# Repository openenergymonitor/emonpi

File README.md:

# emonPi

Raspberry Pi based energy Monitoring Unit

## Documentation

- [Install Guide](https://docs.openenergymonitor.org/emonpi/install.html)
- [Connect](https://docs.openenergymonitor.org/emonpi/connect.html)
- [Pulse counting](https://docs.openenergymonitor.org/emonpi/pulse_counting.html)
- [Temperature sensing](https://docs.openenergymonitor.org/emonpi/temperature_sensing.html)
- [Firmware](https://docs.openenergymonitor.org/emonpi/firmware.html)
- [Configuration](https://docs.openenergymonitor.org/emonpi/configuration.html)
- [Use in North America](https://docs.openenergymonitor.org/emonpi/north-america.html)
- [Modification](https://docs.openenergymonitor.org/emonpi/modification.html)
- [Technical](https://docs.openenergymonitor.org/emonpi/technical.html)

Or view directly on github [here](docs).

## [emonSD image download](https://docs.openenergymonitor.org/emonsd/download.html)

[Software Stack Build & Documentation](https://github.com/openenergymonitor/emonscripts)

## Open-Hardware:

- [Schematic & Board CAD Design Files](https://github.com/openenergymonitor/emonpi/tree/master/hardware)

## Community & Support

- [OpenEnergyMonitor Forums](https://community.openenergymonitor.org)
- OpenEnergyMonitor Shop Support: support@openenergymonitor.zendesk.com

## License

- The hardware designs (schematics and CAD files) are licensed under a Creative Commons Attribution-ShareAlike 3.0 Unported License.
- The firmware is released under the GNU GPL V3 license The documentation is subject to GNU Free Documentation License
- The hardware designs follow the terms of the OSHW (Open-source hardware) Statement of Principles 1.0.

## Disclaimer

```
OUR PRODUCTS AND ASSEMBLY KITS MAY BE USED BY EXPERIENCED, SKILLED USERS, AT THEIR OWN RISK. TO THE FULLEST EXTENT PERMISSIBLE BY THE APPLICABLE LAW, WE HEREBY DISCLAIM ANY AND ALL RESPONSIBILITY, RISK, LIABILITY AND DAMAGES ARISING OUT OF DEATH OR PERSONAL INJURY RESULTING FROM ASSEMBLY OR OPERATION OF OUR PRODUCTS.

Your safety is your own responsibility, including proper use of equipment and safety gear, and determining whether you have adequate skill and experience. OpenEnergyMonitor and Megni registered partnership disclaims all responsibility for any resulting damage, injury, or expense. It is your responsibility to make sure that your activities comply with applicable laws, including copyright. Always check the webpage associated with each unit before you get started. There may be important updates or corrections. All use of the instructions, kits, projects and suggestions given both by megni.co.uk, openenergymonitor.org and shop.openenergymonitor.org are to be used at your own risk. The technology (hardware , firmware and software) are constantly changing, documentation (including build guide and instructions) may not be complete or correct.

If you feel uncomfortable with assembling or using any part of the system, return it to us for a full refund.
```

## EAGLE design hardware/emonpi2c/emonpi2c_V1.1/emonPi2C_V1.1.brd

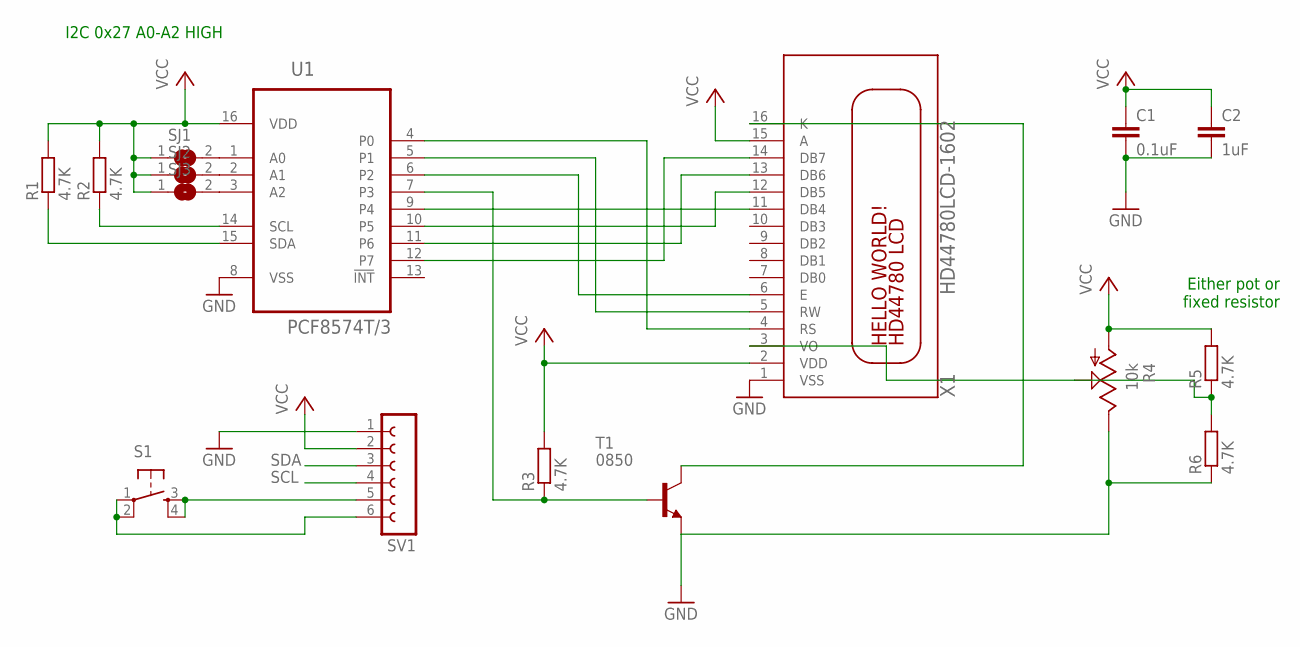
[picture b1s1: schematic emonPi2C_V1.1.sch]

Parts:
C1: 0.1uF; C0603
C2: 1uF; C0603
R1, R2, R3, R5, R6: 4.7K; R0603
R4: 10k; B25P
S1: TAC_SWITCHPTH; TACTILE-PTH
SJ1, SJ2, SJ3: SJ
SV1: FE06-1; FE06
T1: 0850; SOT23
U1: PCF8574T/3; SOIC127P1032X265-16N
X1: HD44780LCD-1602; LCD1602

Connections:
5V: C1.1, C2.1, R1.2, R2.2, R3.2, R4.A, R5.2, SJ1.1, SJ2.1, SJ3.1, SV1.2, U1.16 (VDD), X1.2 (VDD), X1.15 (A)
CS: U1.6 (P2), X1.6 (E)
DB4: U1.9 (P4), X1.11 (DB4)
DB5: U1.10 (P5), X1.12 (DB5)
DB6: U1.11 (P6), X1.13 (DB6)
DB7: U1.12 (P7), X1.14 (DB7)
GND: C1.2, C2.2, R4.E, R6.1, SV1.1, T1.2 (E), U1.8 (VSS), X1.1 (VSS)
K: T1.3 (C), X1.16 (K)
unnamed: SJ3.2, U1.3 (A2)
unnamed: SJ2.2, U1.2 (A1)
unnamed: S1.3, S1.4, SV1.5
unnamed: S1.1, S1.2, SV1.6
unnamed: SJ1.2, U1.1 (A0)
unnamed: R4.S, R5.1, R6.2, X1.3 (VO)
P3: R3.1, T1.1 (B), U1.7 (P3)
RS: U1.4 (P0), X1.4 (RS)
RW: U1.5 (P1), X1.5 (RW)
SCL: R2.1, SV1.4, U1.14 (SCL)
SDA: R1.1, SV1.3, U1.15 (SDA)

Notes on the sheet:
Either pot or fixed resistor
I2C 0x27 A0-A2 HIGH

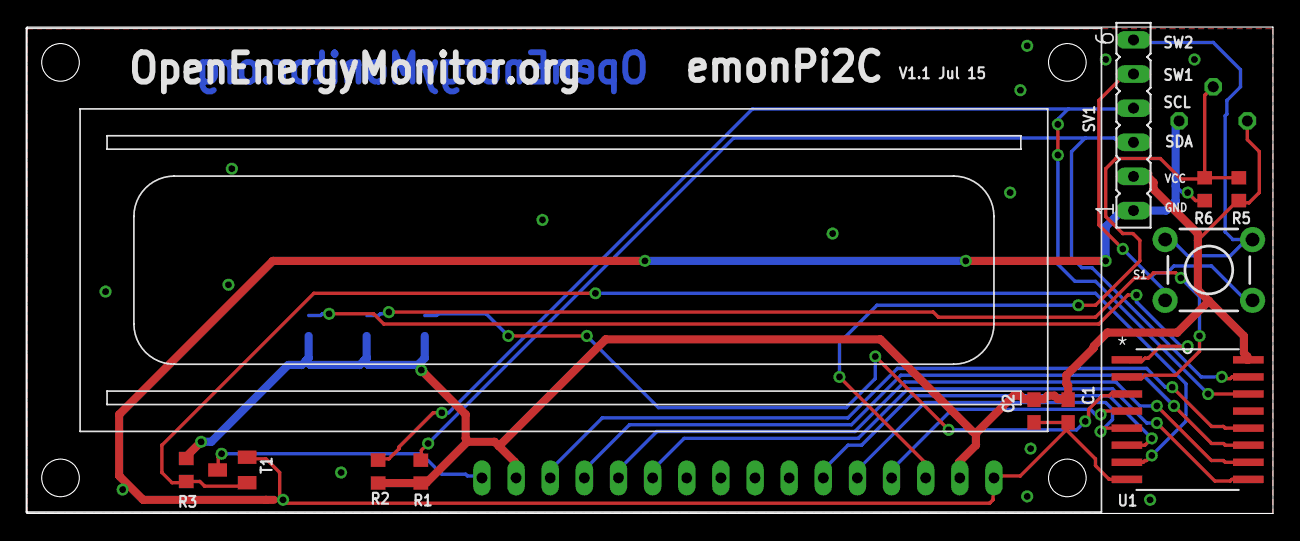
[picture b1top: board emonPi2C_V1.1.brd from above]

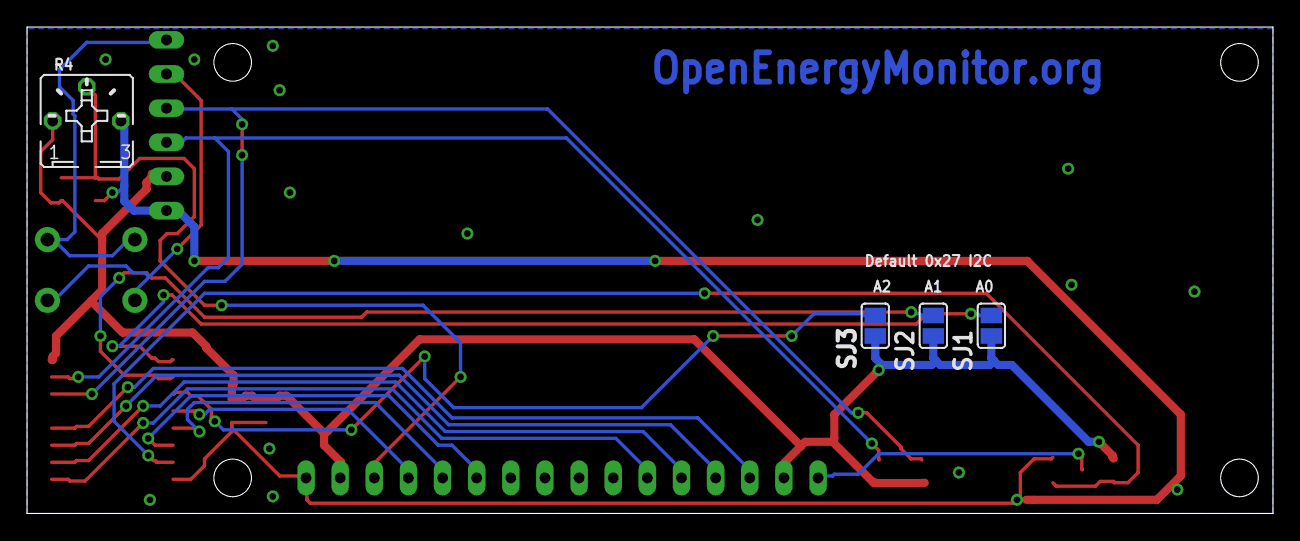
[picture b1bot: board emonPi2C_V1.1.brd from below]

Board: 2 copper layers, 92.7 x 36.2 mm, 16 parts (4 on the bottom side), 19 nets.

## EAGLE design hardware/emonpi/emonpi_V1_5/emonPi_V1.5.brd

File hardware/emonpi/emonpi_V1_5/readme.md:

## emonPi V1.5

**Raspberry Pi Energy Monitoring Shield**

### Schematic

### Board

### Open Hardware

Hardware designs (schematics and CAD) files are licensed under the [Creative Commons Attribution-ShareAlike 3.0 Unported License](http://creativecommons.org/licenses/by-sa/3.0/) and follow the terms of the [OSHW (Open-source hardware) Statement of Principles 1.0.](http://freedomdefined.org/OSHW)

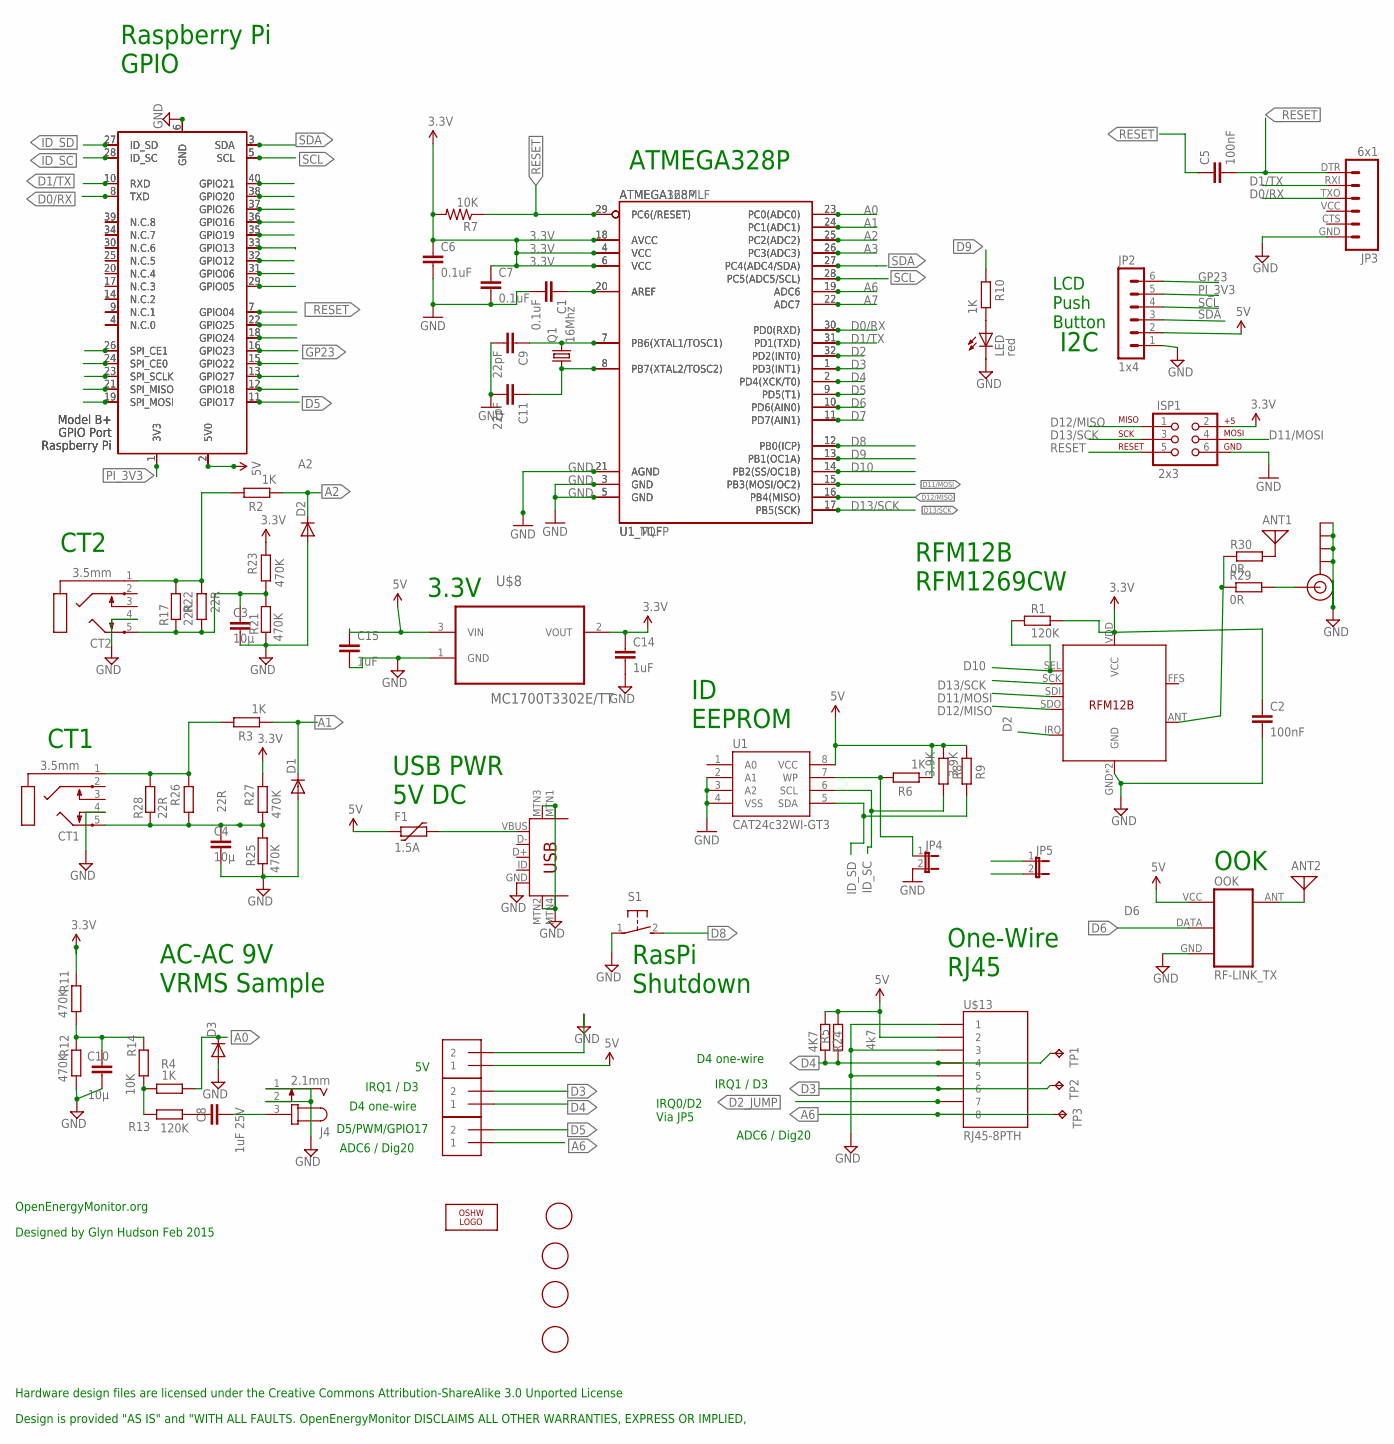
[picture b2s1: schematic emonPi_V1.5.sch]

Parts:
ANT1, ANT2: ANTENNA; PAD-01
C1, C6, C7: 0.1uF; C0603
C2, C5: 100nF; C0603
C3, C4, C10: 10µ; C0603
C8: 1uF 25V; C0603
C9, C11: 22pF; C0603
C14, C15: 1uF; C0603
CT1, CT2: 3.5mm; STX3100
D1, D2, D3: DIODE-SOD523; SOD523
F1: 1.5A; PTC1812L
ISP1: 2x3; 2X3
J1, J2, J3: 1X2-3.5MM
J4: 2.1mm; SPC4077
J$1: SMA_EDGE; SMA-EDGE
JP2: 1x4; MA06-1
JP3: 6x1; FTDI_BASIC
JP4, JP5: JUMPER-2PTH; 1X02
LED: red; CHIPLED_0805
LOGO1: OSHW_LOGO_10MILX0200-NT; OSHW_10X200_NOTEXT
OOK: RF-LINK_TX
Q1: 16Mhz; HC49UP
R1, R13: 120K; R0603
R2, R3, R4, R6, R10: 1K; R0603
R5: 4k7; 0204/7
R7, R14: 10K; R0603
R8, R9: 3.9K; R0603
R11, R12, R21, R23, R25, R27: 470K; R0603
R17, R28: 22R; R1206
R22, R26: 22R; 0204/7
R24: 4K7; R0603
R29, R30: 0R; R0603
S1: 31-XX; B3F-31XX
TP1, TP2, TP3: TPPAD1-13; P1-13
U1: CAT24c32WI-GT3; SO08
U1_MLF: ATMEGA168MLF; MLF32
U1_TQFP: ATMEGA328P; TQFP32-08
U$1, U$3, U$4, U$5: FIDUCIAL; FIDUCIAL_1MM
U$7: USB-MINIB-5PIN; USB-MINIB-CISECO
U$8: MC1700T3302E/TT; SOT95P237X112-3N
U$13: RJ45-8PTH; RJ45-8
U$14: RFM12B
X1: RASPI_GPIO_B+_SMT; RASPI_SMT_GPIO_B+_PIN
X4: RASPI_GPIO_B+_PIN

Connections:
3.3V: C2.1, C6.1, C7.1, C14.1, ISP1.2, R1.2, R7.2, R11.2, R23.2, R27.2, U1_MLF.4 (VCC), U1_MLF.6 (VCC), U1_MLF.18 (AVCC), U1_TQFP.4 (VCC), U1_TQFP.6 (VCC), U1_TQFP.18 (AVCC), U$8.2 (VOUT), U$14.VDD (VCC)
5V: C15.1, F1.1, J1.1, JP2.2, OOK.VCC (+5V), R5.2, R6.1, R8.1, R9.1, R24.1, U1.8 (VCC), U$8.3 (VIN), U$13.2, X1.2 (5V0), X4.2 (5V0)
A0: D3.C, R4.1, U1_MLF.23 (PC0(ADC0)), U1_TQFP.23 (PC0(ADC0))
A1: D1.C, R3.1, U1_MLF.24 (PC1(ADC1)), U1_TQFP.24 (PC1(ADC1))
A2: D2.C, R2.1, U1_MLF.25 (PC2(ADC2)), U1_TQFP.25 (PC2(ADC2))
A3: U1_MLF.26 (PC3(ADC3)), U1_TQFP.26 (PC3(ADC3))
A6: J3.1, TP3.TP, U1_MLF.19 (ADC6), U1_TQFP.19 (ADC6), U$13.8
A7: U1_MLF.22 (ADC7), U1_TQFP.22 (ADC7)
D0/RX: JP3.TXO (3), U1_MLF.30 (PD0(RXD)), U1_TQFP.30 (PD0(RXD)), X1.8 (TXD), X4.8 (TXD)
D1/TX: JP3.RXI (2), U1_MLF.31 (PD1(TXD)), U1_TQFP.31 (PD1(TXD)), X1.10 (RXD), X4.10 (RXD)
D2: JP5.1, U1_MLF.32 (PD2(INT0)), U1_TQFP.32 (PD2(INT0)), U$14.IRQ
D2_JUMP: JP5.2, U$13.7
D3: J2.2, TP2.TP, U1_MLF.1 (PD3(INT1)), U1_TQFP.1 (PD3(INT1)), U$13.6
D4: J2.1, R5.1, R24.2, TP1.TP, U1_MLF.2 (PD4(XCK/T0)), U1_TQFP.2 (PD4(XCK/T0)), U$13.4
D5: J3.2, U1_MLF.9 (PD5(T1)), U1_TQFP.9 (PD5(T1)), X1.11 (GPIO17), X4.11 (GPIO17)
D6: OOK.DATA, U1_MLF.10 (PD6(AIN0)), U1_TQFP.10 (PD6(AIN0))
D7: U1_MLF.11 (PD7(AIN1)), U1_TQFP.11 (PD7(AIN1))
D8: S1.2 (S), U1_MLF.12 (PB0(ICP)), U1_TQFP.12 (PB0(ICP))
D9: R10.2, U1_MLF.13 (PB1(OC1A)), U1_TQFP.13 (PB1(OC1A))
D10: R1.1, U1_MLF.14 (PB2(SS/OC1B)), U1_TQFP.14 (PB2(SS/OC1B)), U$14.SEL
D11/MOSI: ISP1.4, U1_MLF.15 (PB3(MOSI/OC2)), U1_TQFP.15 (PB3(MOSI/OC2)), U$14.SDI
D12/MISO: ISP1.1, U1_MLF.16 (PB4(MISO)), U1_TQFP.16 (PB4(MISO)), U$14.SDO
D13/SCK: ISP1.3, U1_MLF.17 (PB5(SCK)), U1_TQFP.17 (PB5(SCK)), U$14.SCK
DIG6: R29.1, R30.1, U$14.ANT
GND: C1.2, C2.2, C3.2, C4.2, C6.2, C7.2, C9.2, C10.2, C11.2, C14.2, C15.2, CT1.4, CT2.4, D1.A, D2.A, D3.A, ISP1.6, J1.2, J4.1, J4.2, J$1.GND@0 (GND), J$1.GND@1 (GND), J$1.GND@2 (GND), J$1.GND@3 (GND), JP2.1, JP3.GND (6), JP4.2, LED.C, OOK.GND, R12.1, R21.2, R25.2, S1.1, U1.2 (A1), U1.3 (A2), U1.4 (VSS), U1_MLF.3 (GND), U1_MLF.5 (GND), U1_MLF.21 (AGND), U1_TQFP.3 (GND), U1_TQFP.5 (GND), U1_TQFP.21 (AGND), U$7.GND, U$7.MTN1 (MTN2), U$7.MTN2 (MTN3), U$7.MTN3 (MTN1), U$7.MTN4, U$8.1 (GND), U$13.1, U$13.3, U$13.5, U$14.GND, U$14.P$12 (GND), X1.6 (GND), X4.6 (GND)
GP23: JP2.6, X1.16 (GPIO23), X4.16 (GPIO23)
ID_SC: R8.2, U1.6 (SCL), X1.28 (ID_SC), X4.28 (ID_SC)
ID_SD: R9.2, U1.5 (SDA), X1.27 (ID_SD), X4.27 (ID_SD)
unnamed: C9.1, Q1.2, U1_MLF.7 (PB6(XTAL1/TOSC1)), U1_TQFP.7 (PB6(XTAL1/TOSC1))
unnamed: C11.1, Q1.1, U1_MLF.8 (PB7(XTAL2/TOSC2)), U1_TQFP.8 (PB7(XTAL2/TOSC2))
unnamed: C3.1, CT2.5, R17.1, R21.1, R22.1, R23.1
unnamed: C8.1, R13.1
unnamed: R4.2, R13.2, R14.1
unnamed: CT1.1, R3.2, R26.2, R28.2
unnamed: ANT1.1, R30.2
unnamed: ANT2.1, OOK.ANT
unnamed: C4.1, CT1.5, R25.1, R26.1, R27.1, R28.1
unnamed: F1.2, U$7.VBUS
unnamed: CT2.1, R2.2, R17.2, R22.2
unnamed: C8.2, J4.3
unnamed: C1.1, U1_MLF.20 (AREF), U1_TQFP.20 (AREF)
unnamed: J$1.SIG (SIGNAL), R29.2
unnamed: X1.12 (GPIO18), X4.12 (GPIO18)
unnamed: X1.13 (GPIO27), X4.13 (GPIO27)
unnamed: X1.15 (GPIO22), X4.15 (GPIO22)
unnamed: C10.1, R11.1, R12.2, R14.2
unnamed: X1.18 (GPIO24), X4.18 (GPIO24)
unnamed: X1.22 (GPIO25), X4.22 (GPIO25)
unnamed: LED.A, R10.1
unnamed: X1.19 (SPI_MOSI), X4.19 (SPI_MOSI)
unnamed: X1.21 (SPI_MISO), X4.21 (SPI_MISO)
unnamed: X1.23 (SPI_SCLK), X4.23 (SPI_SCLK)
unnamed: X1.24 (SPI_CE0), X4.24 (SPI_CE0)
unnamed: X1.26 (SPI_CE1), X4.26 (SPI_CE1)
unnamed: X1.4 (N.C.0), X4.4 (N.C.0)
unnamed: X1.9 (N.C.1), X4.9 (N.C.1)
unnamed: X1.14 (N.C.2), X4.14 (N.C.2)
unnamed: X1.17 (N.C.3), X4.17 (N.C.3)
unnamed: X1.20 (N.C.4), X4.20 (N.C.4)
unnamed: X1.25 (N.C.5), X4.25 (N.C.5)
unnamed: X1.29 (GPIO05), X4.29 (GPIO05)
unnamed: X1.31 (GPIO06), X4.31 (GPIO06)
unnamed: X1.32 (GPIO12), X4.32 (GPIO12)
unnamed: X1.33 (GPIO13), X4.33 (GPIO13)
unnamed: X1.35 (GPIO19), X4.35 (GPIO19)
unnamed: X1.36 (GPIO16), X4.36 (GPIO16)
unnamed: X1.37 (GPIO26), X4.37 (GPIO26)
unnamed: X1.38 (GPIO20), X4.38 (GPIO20)
unnamed: X1.40 (GPIO21), X4.40 (GPIO21)
unnamed: X1.30 (N.C.6), X4.30 (N.C.6)
unnamed: X1.34 (N.C.7), X4.34 (N.C.7)
unnamed: X1.39 (N.C.8), X4.39 (N.C.8)
unnamed: JP4.1, R6.2, U1.7 (WP)
PI_3V3: JP2.5, X1.1 (3V3), X4.1 (3V3)
RESET: C5.1, ISP1.5, R7.1, U1_MLF.29 (PC6(/RESET)), U1_TQFP.29 (PC6(/RESET))
SCL: JP2.4, U1_MLF.28 (PC5(ADC5/SCL)), U1_TQFP.28 (PC5(ADC5/SCL)), X1.5 (SCL), X4.5 (SCL)
SDA: JP2.3, U1_MLF.27 (PC4(ADC4/SDA)), U1_TQFP.27 (PC4(ADC4/SDA)), X1.3 (SDA), X4.3 (SDA)
_RESET: C5.2, JP3.DTR (1), X1.7 (GPIO04), X4.7 (GPIO04)

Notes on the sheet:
AC-AC 9V VRMS Sample
OpenEnergyMonitor.org
Designed by Glyn Hudson Feb 2015
Hardware design files are licensed under the Creative Commons Attribution-ShareAlike 3.0 Unported License
Design is provided "AS IS" and "WITH ALL FAULTS. OpenEnergyMonitor DISCLAIMS ALL OTHER WARRANTIES, EXPRESS OR IMPLIED,
D4 one-wire
IRQ1 / D3
ADC6 / Dig20
D5/PWM/GPIO17
USB PWR 5V DC
RasPi Shutdown
I2C
RFM12B RFM1269CW
OOK
One-Wire RJ45
CT1
CT2
Raspberry Pi GPIO
ATMEGA328P
LCD Push Button
ID EEPROM
IRQ0/D2 Via JP5
3.3V

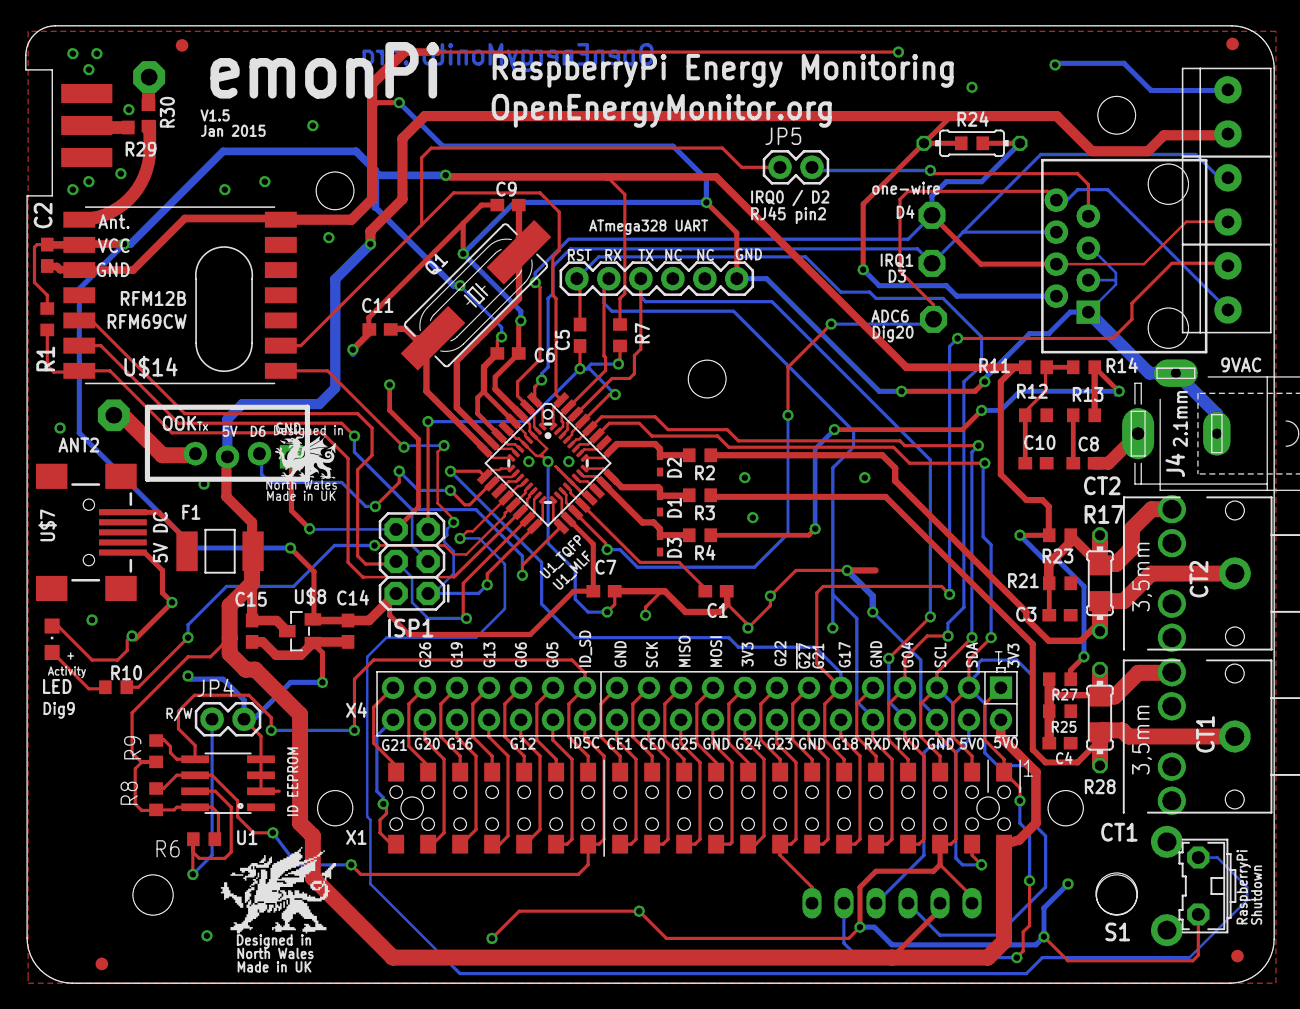
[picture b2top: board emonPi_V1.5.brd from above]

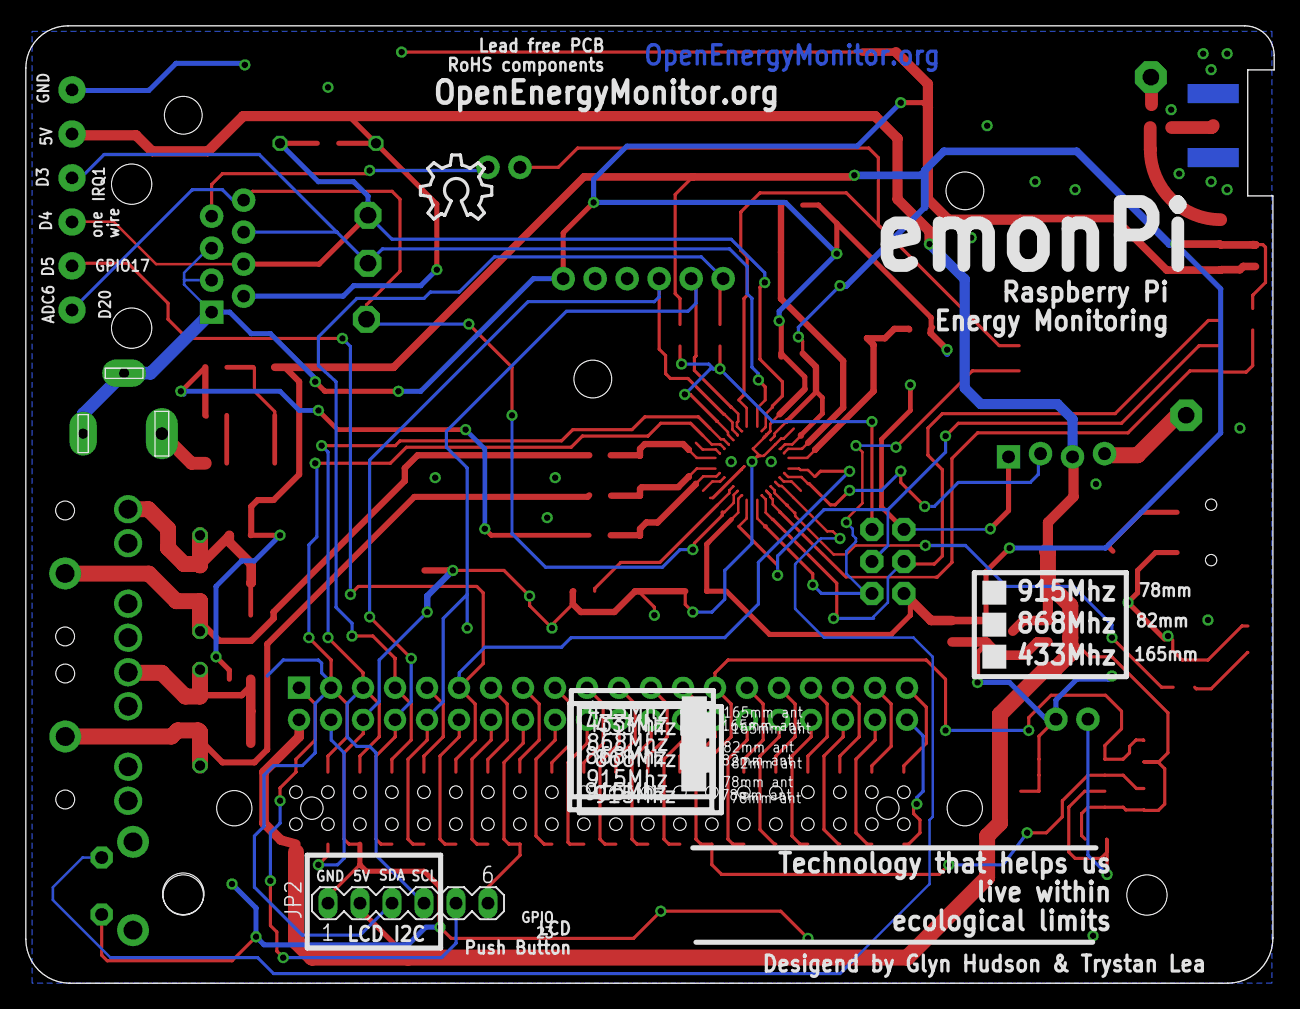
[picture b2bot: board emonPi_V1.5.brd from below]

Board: 2 copper layers, 99.1 x 76.0 mm, 78 parts (2 on the bottom side), 78 nets.

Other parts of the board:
U$9: STAND-OFF

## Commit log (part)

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2018-06-24 use more reliable wifi-check logic
2018-06-24 restart interface is require, belt and braces wifi check script
2018-08-21 clone / update device model
2018-08-23 Rewrite service-runner in Python
    Since the switch to redis, the bash script version of service-runner causes unnecessary load on redis due to having to create a new connection every iteration of the loop. Rewriting it in Python uses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
2018-08-23 add Stretch specific config files & modify WiFi AP to work on both Jessie & Stretch
2018-08-23 Add python emonPi LCD install instructions to readme
2018-08-24 Changed from Cron triggered to systemd
2018-08-24 Fixed copy/paste spacing issue while trying to tidy up commits.
2018-08-24 add new service runner install instructions
2018-08-26 update install instructions
2018-08-26 add instructions to view log
2018-08-28 Now gracefully handles redis-server stopping / starting. Script will continuously retry connection waiting 30 seconds between attempts.
2018-08-28 Removed sudo from commands where it is not actually required
2018-08-28 Fixed an exception related to the 'touch' functionality (missing import os)
2018-10-15 add push and hold example using new lib
2018-10-15 enable ssh via a 5s long press
2018-10-17 improve MQTT connection
2018-10-17 remove add file system indicator and emonpixel
2018-10-17 add new emonSD image to update list
2018-10-18 remove connectivity check dealy on first boot
2018-10-18 set permissions of wpa_supplicant
2018-10-18 add version control to Emoncms Setup module
2018-10-18 add note for unused stretch fstab
2018-10-18 fix formatting
2018-10-20 Correction to versions
    Commit https://github.com/openenergymonitor/emonpi/commit/ef63fd52edb5e96ba0189d938df953c583cd612d broke support for the current latest image "emonSD-26Oct17".
    See https://community.openenergymonitor.org/t/after-update-to-9-9-0-process-list-all-unavaiblable/8893/7?u=pb66
2018-10-22 don't add service runner manually or run update during factory reset
2018-10-22 make factoryreset runable
2018-10-22 correctly restart new service runner
2018-10-26 define monitor baud
2018-10-27 add shebang to fix emoncms/emoncms/#1089
2018-10-30 LCD script improvments: error handling, AP mode display
2018-11-06 confirm apt install
2018-11-19 Update service-runner-update.sh
    Line 138 is not outputting the new line for the \n because echo doesn't understand those.
    either change to printf, or to "echo -e" and remove the "\n"
2018-11-25 add dependency on DS2438 library to platformio.ini
2018-11-27 Added configuration file for emonPiLCD.py Allows user to tweak config and choose other values for display for the power readings (for example, if an external power meter is being used)
    Fixed issue with backlight=0 , and default page is now the power
    readings. Useful if emonpi is in a dark cupboard (as they usually are)
2018-11-27 Defaults set correctly for emonpi
2018-11-27 Reduce Pi CPU usage by 30 - 40% ! The emonPiLCD.py script has been refactored to properly use the button Callback and only workout values for the LCD on a button press
    Previous there was a crazy while (true) loop which constantly battered
    the Pi and REDIS causing massive CPU usage.
    This should leave a lot more headroom for things like openhab and make
    the pi more responsive.
    The shutdown button has also been moved to a callback, avoiding the need
    to poll constantly. It activates on 'long press'
2018-11-27 fix default ssh password
2018-11-28 Fix non-initialise variable error for GSM when eth but no wifi In other words, initialise redis eth,wlan and gsm variables in main()
2018-12-04 Added Shutdown & Ssh menu to main push button Long hold turns off backlight
2018-12-06 set default IP address LCD display
2018-12-06 Bump version V3.0.0
2018-12-06 create openhab2 log folders
2018-12-10 change sshd to ssh
2018-12-12 fix non-zero LCD timeout
2019-01-07 added blank files to identify device type during boot
2019-01-15 install rng-tools
    https://community.openenergymonitor.org/t/cant-connect-to-local-emoncms/9498/7
2019-01-31 installation correction for feedwriter and mqtt_input services
2019-02-06 improved service installation section
2019-02-07 daemon reload any potential service changes
2019-02-07 improve emonsd detection
2019-02-07 emonSD_pi_env
2019-02-07 kill phpmqtt_input still running
2019-02-07 switch to systemd emonhub.service
2019-02-21 add www-data to systemd-journal to view emonhub systemd log in Emoncms emonhub config module
2019-02-21 Update emonhub-sudoers
2019-02-21 only run rpi-rw/ro if read-only fs is enabled
2019-03-18 deploy emoncms logroate config
2019-03-18 improve logrotate deploy
2019-03-25 update refactor
2019-03-25 wifi-sudoers already in sudoers.d
2019-03-25 split out install and remove emoncms services
2019-03-25 configurable homedir
2019-03-25 pass username as argument
2019-03-26 select update type (use with emoncms: update_concept branch)
2019-03-26 use /usr/emoncms/modules if available
2019-03-26 autodetect path
2019-03-26 fix module install path
2019-03-28 emonSD build script
2019-03-28 include all emonpi update commands
2019-03-28 move image check to service runner update
2019-03-28 use original complete string
2019-03-28 move image check back to main.sh
2019-03-28 images that are safe to update
2019-03-28 place os and package updates in pi env check
2019-04-02 work on modularising install script
2019-04-02 breakout settings
2019-04-02 install script, config.ini
2019-04-02 fix config load issue
2019-04-02 use bin/bash
2019-04-02 tested install process
2019-04-02 updated install script for emonPiLCD
2019-04-03 install process improvements
2019-04-03 - fix python redis client - set new backup module config placeholders
2019-04-03 run backup install.sh
2019-04-05 auto run emoncms module install.sh script (handles service installation)
2019-04-05 emonhub service installation modify exec path
2019-04-05 remove usrdir requirement for emonhub install script
2019-04-05 change permissions of log directory
2019-04-05 flexible path to test
2019-04-08 wifiAP setup
2019-04-08 change datadir to /var/opt
2019-04-08 remove cd
2019-04-08 symlink backup module
2019-04-12 cleanup wifi sudoers
2019-04-12 update process to support merged backup module
2019-04-12 update install script to use backup module master branch
2019-04-15 support for setting repo branch in config.ini
2019-04-25 use systemctl
2019-04-25 optional install of mosquitto server/client
2019-04-25 use username running script
2019-04-25 ext2 partition installation notes
2019-04-25 Update fstab
2019-05-03 correctly configure mariadb service
2019-05-04 also mkdir during script install
2019-05-07 Revise mariadb ProtectHome fix
    Removed "fix" from install script as not required.
    Changed update to write file rather than cp so that there is no need for a copy of the file in the repo (as not needed down the line). Removed repo copy of redundant file.
2019-05-07 Better improve the test for mysql location
2019-05-20 Update emoncms.sh
    Update according to https://community.openenergymonitor.org/t/switching-branch/10809
2019-05-22 Create emonhub conf symlink in /etc/emonhub
2019-05-29 Update safe-update
    add emonSD-07Nov16
2019-06-04 add emonhub.env settings file and install as part of update
2019-06-12 symlink emonpiupdate.log as part of update auto create /var/log/emoncms on jessie
2019-06-17 use /usr/local/bin/emonhub
2019-08-08 Update emoncms.sh
    allow for updating of sudoers file
2019-08-09 Update hello.php
    provide feedback on set config
2019-08-23 Use `git fetch` to update tags
    A `git fetch --prune` is required to ensure the tags get updated and so the 'git describe' used in the admin screen reports correctly. Including an `--all` just simply updates the local & remote repo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
2019-09-26 - only upgrade settings.php if present - switch postprocess branch to stable
2019-09-26 switch device module and sync module to stable branch
2019-09-26 switch branches only if core is stable
2019-09-26 git fetch before git pull
2019-09-26 settings_object support
2019-09-26 wifi scan support for settings object
2019-10-04 exit without failure state if emonbase
2019-10-14 note on running as root
2019-10-17 Fix whitespace, spelling.
2019-10-17 Tidy up other scripts
2019-10-17 Python2/3 compatibility.
2019-10-17 Fix dodgy merge commit 53a34285.
2019-11-17 fix RFM init
    https://community.openenergymonitor.org/t/emonpi-firmware-build/12428/45
2019-11-17 bump version V2.9.2
2020-01-02 Remove unnecessary logging.shutdown call.
    [https://docs.python.org/3/library/logging.html#logging.shutdown]
    When the logging module is imported, it registers this function as
    an exit handler (see atexit), so normally there’s no need to do that
    manually.
2020-01-03 Migrate to Python 3.
2020-02-06 Python3
2020-03-30 More Python3 fixes.
2020-06-14 Update emonPiLCD.py
    to solve conflict
2020-06-14 check_output is already returning string.
2020-06-14 sd_image_version is already a string
2020-06-14 Simplify lcd driver.
    - Remove i2c_lib. We're only using one function.
2020-06-14 Avoid subprocess to detect SD image version.
2020-06-14 Add a degree sign for the temperature pages.
2020-06-14 Remove unnecessary global.
    global is only required when assigning to a name within a function, to
    disambiguate between a local variable with the same name. These
    functions don't assign to these names, so global is misleading.
2020-06-24 chmod +x install.sh
2020-06-25 correction in service file
2020-06-25 correction in service file, emonPiLCD service has to be launched after mosquitto.service
2020-06-25 adding sudo for shutdown
2020-06-28 adding sudo to ssh commands....
2020-07-01 Update install.sh
    removing the test on the python version
2020-07-29 Provide more output in the network log
2020-08-02 apt-get update already run from EmonScripts
2020-08-03 update to support python3
2020-08-03 update service description
2020-08-05 release V2.9.2 FW as latest available via emonpi update
2020-08-22 Save wificheck.log to tmpfs-backed /var/log
    I have a emonpi which is used for forwarding all data from emonTX/emonTH to my server hosting Emoncms. It itself doesn't save any incoming data.
    Few days earlier I login to it and discovered that /home/pi/data is still being written, and the only file with recent mtime is wificheck.log.
    Given that wifi-check is only used for restarting wifi connection I think saving its log to /var/log would be OK, and this can prolong the life of SD card.
2020-08-26 display RasPi serial number on LCD
2020-08-31 Fix TypeError with python >= 2.x
    Traceback (most recent call last):
    File "/home/pi/emonpi/md5sum.py", line 20, in <module>
    md5_returned = hashlib.md5(data).hexdigest()
    TypeError: Unicode-objects must be encoded before hashing
2021-01-05 take longer for DJ18B20 temp conversion, bump version V2.9.3
2021-01-05 change log
2021-05-17 module.json file
2021-10-17 Add link to emon scripts for software stack build
2021-10-21 remove add ap flag in right directory
2022-02-07 bump version number
2022-02-25 bump FW version number to match release
2022-02-25 add V2.9.5 pre-compiled firmware
2022-11-24 relocate install guide
2022-12-01 fix note syntax
2022-12-02 add emonpi technical from guide
2023-01-23 documentation migration
2023-01-24 wiki migration
2023-01-24 modification link
2023-01-24 fix image link
2023-02-06 Update credentials
2023-02-16 update emonPi_CM version
2023-02-16 emonPi_CM
2023-02-17 remove pdf
2023-03-29 include ACK mechanism
2023-04-04 updated to use cut down version of RFM69 LPL library
2023-04-04 fix version and native compile
2023-04-17 update platformio to use main RFM69_LPL library
2023-04-18 suggest same nodename for node decoder
2023-04-19 update change log
2023-11-17 support for both emonPi versions
2023-11-17 emonpiLCD scripts
2023-11-17 fix error
2023-11-17 change order
2023-11-17 only import relevant subscript
2023-12-08 fix pullup
2023-12-18 Updated wifi implementation
2024-01-03 remove moved scripts
2024-01-04 enable and disable ap0
2024-01-05 show client wifi at all times
2024-05-08 Fix MQTT topic selection from config file Format temp and vrms to .2f Allow emonPiLCD1.py to work with both emonlibCM and DS firmware

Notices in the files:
parts and their libraries:
SparkFun-RF: Licensing: CC v3.0 Share-Alike You are welcome to use this library for commercial purposes.
